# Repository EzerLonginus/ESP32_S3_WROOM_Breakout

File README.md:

# ESP32_S3_WROOM_Breakout
Breakout Board for ESP32 S3 WROOM

This board is a simple breakout for the ESP32 S3 WROOM.  The interface includes the standard reset and boot button, with a USB to UART CH340G converter, and a 3V3 regulator.  All GPIO pins are broken out to standard 2.54mm headers.  USB-C reseptacle connector is used, but at the USB 2.0 standard. 

## Purpose
This is mostly an excersize in designing an ESP32 module for inclusion in other projects.  Once this design is functional, I'll start using it as a template for more custom oriented projects involving the chip (or some variant).  I decided on the ESP S3 WROOM, because the S2 Solo seems to be slowly phasing out, and also doesn't have bluetooth functionality.  Depending on how this excersize goes, I may start designing boards with just the bare chip (no built in WiFi antenna, SPI Flash, etc).    

## Scematic

## Layout

## Current State of Affairs
### Version 1
* Populate and test board
* Upload some blink/hello world sketch
* Fix the inevitable issue that I missed during production

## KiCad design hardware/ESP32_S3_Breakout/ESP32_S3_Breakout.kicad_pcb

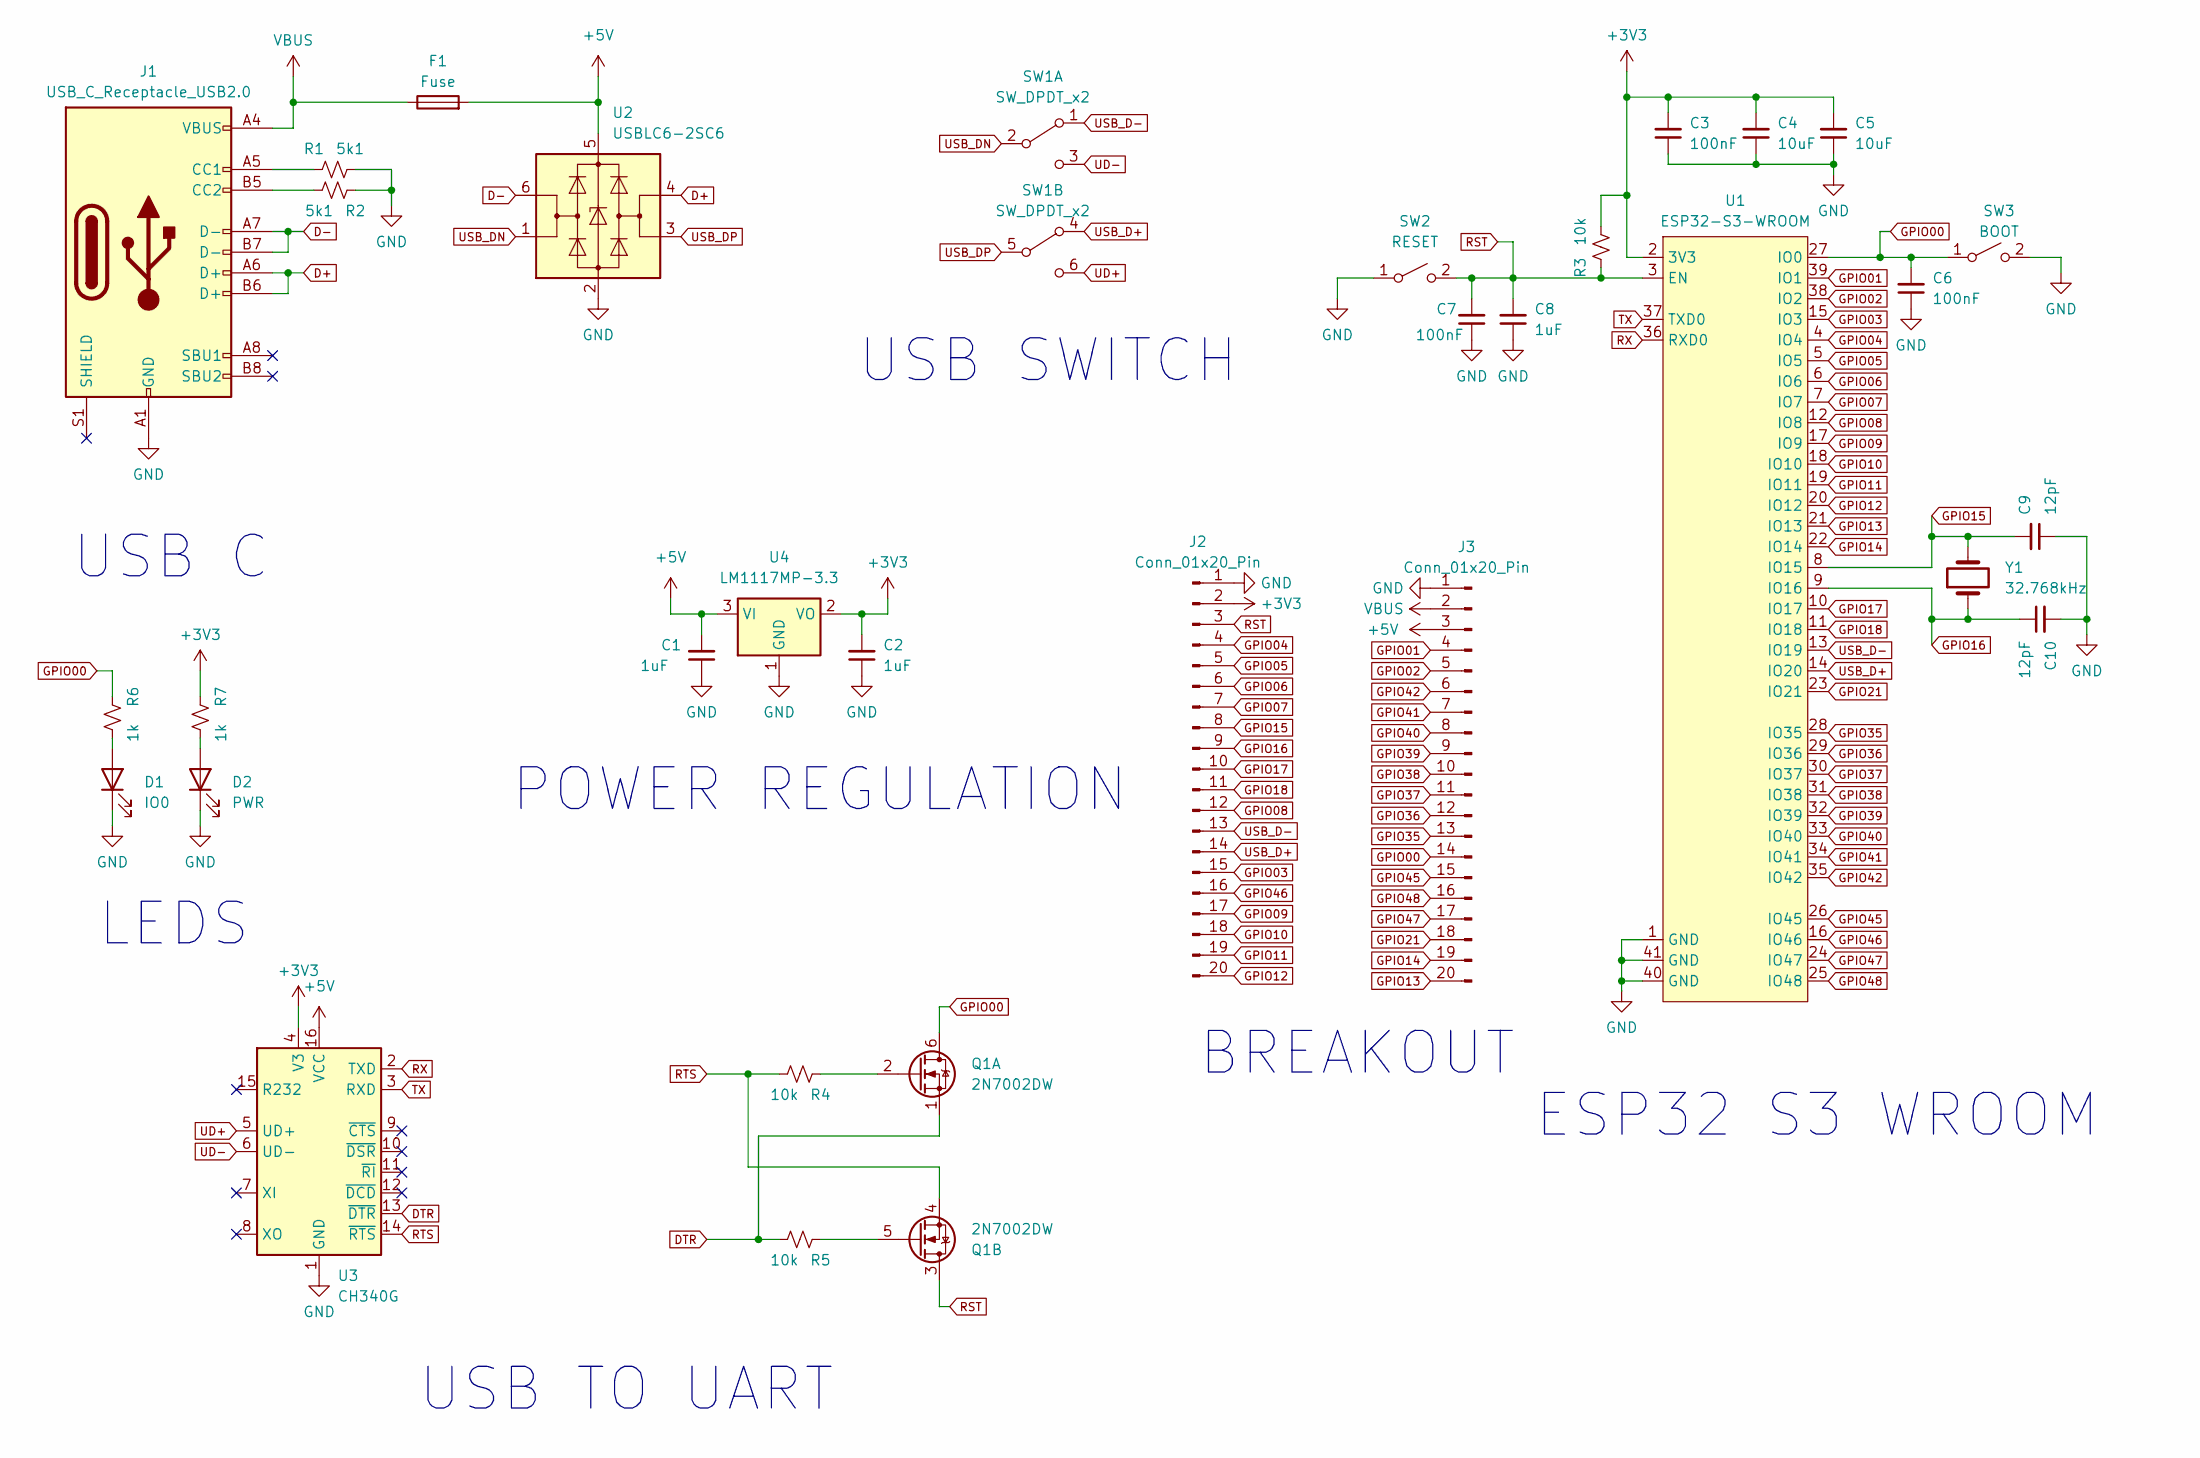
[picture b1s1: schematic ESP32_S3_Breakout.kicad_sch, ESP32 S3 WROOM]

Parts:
C1, C2, C8: 1uF; C_0603_1608Metric
C3, C6, C7: 100nF; C_0603_1608Metric
C4, C5: 10uF; C_0805_2012Metric
C9, C10: 12pF; C_0603_1608Metric
D1: IO0; LED_0603_1608Metric
D2: PWR; LED_0603_1608Metric
F1: Fuse; Fuse_0603_1608Metric
J1: USB_C_Receptacle_USB2.0; USB_C_Receptacle_G-Switch_GT-USB-7010ASV
J2, J3: Conn_01x20_Pin; PinHeader_1x20_P2.54mm_Vertical
Q1: 2N7002DW; SOT-363_SC-70-6
R1, R2: 5k1; R_0603_1608Metric
R3, R4, R5: 10k; R_0603_1608Metric
R6, R7: 1k; R_0603_1608Metric
SW1: SW_DPDT_x2; SMD DPDT Toggle SS-3235S-L1
SW2: RESET; SW_SPST_CK_RS282G05A3
SW3: BOOT; SW_SPST_CK_RS282G05A3
U1: ESP32-S3-WROOM; ESP32-S3-WROOM-1
U2: USBLC6-2SC6; SOT-23-6
U3: CH340G; SOIC-16_3.9x9.9mm_P1.27mm
U4: LM1117MP-3.3; SOT-223-3_TabPin2
Y1: 32.768kHz; Crystal_SMD_EuroQuartz_EQ161-2Pin_3.2x1.5mm_HandSoldering

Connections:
+3V3: C2.2, C3.2, C4.2, C5.2, J2.2, R3.2, R7.1, U1.2 (3V3), U3.4 (V3), U4.2 (VO)
+5V: C1.2, F1.2, J3.3, U2.5 (VBUS), U3.16 (VCC), U4.3 (VI)
D+: J1.A6 (D+), J1.B6 (D+), U2.4 (I/O2)
D-: J1.A7 (D-), J1.B7 (D-), U2.6 (I/O1)
DTR: Q1.1 (S), R5.2, U3.13 (~DTR)
GND: C1.1, C2.1, C3.1, C4.1, C5.1, C6.1, C7.1, C8.1, C9.1, C10.2, D1.1 (K), D2.1 (K), J1.A1 (GND), J1.A12 (GND), J1.B1 (GND), J1.B12 (GND), J2.1, J3.1, R1.2, R2.1, SW2.1 (A), SW3.2 (B), U1.1 (GND), U1.40 (GND), U1.41 (GND), U2.2 (GND), U3.1 (GND), U4.1 (GND)
GPIO00: C6.2, J3.14, Q1.6 (D), R6.1, SW3.1 (A), U1.27 (IO0)
GPIO01: J3.4, U1.39 (IO1)
GPIO02: J3.5, U1.38 (IO2)
GPIO03: J2.15, U1.15 (IO3)
GPIO04: J2.4, U1.4 (IO4)
GPIO05: J2.5, U1.5 (IO5)
GPIO06: J2.6, U1.6 (IO6)
GPIO07: J2.7, U1.7 (IO7)
GPIO08: J2.12, U1.12 (IO8)
GPIO09: J2.17, U1.17 (IO9)
GPIO10: J2.18, U1.18 (IO10)
GPIO11: J2.19, U1.19 (IO11)
GPIO12: J2.20, U1.20 (IO12)
GPIO13: J3.20, U1.21 (IO13)
GPIO14: J3.19, U1.22 (IO14)
GPIO15: C9.2, J2.8, U1.8 (IO15), Y1.2
GPIO16: C10.1, J2.9, U1.9 (IO16), Y1.1
GPIO17: J2.10, U1.10 (IO17)
GPIO18: J2.11, U1.11 (IO18)
GPIO21: J3.18, U1.23 (IO21)
GPIO35: J3.13, U1.28 (IO35)
GPIO36: J3.12, U1.29 (IO36)
GPIO37: J3.11, U1.30 (IO37)
GPIO38: J3.10, U1.31 (IO38)
GPIO39: J3.9, U1.32 (IO39)
GPIO40: J3.8, U1.33 (IO40)
GPIO41: J3.7, U1.34 (IO41)
GPIO42: J3.6, U1.35 (IO42)
GPIO45: J3.15, U1.26 (IO45)
GPIO46: J2.16, U1.16 (IO46)
GPIO47: J3.17, U1.24 (IO47)
GPIO48: J3.16, U1.25 (IO48)
unnamed: D1.2 (A), R6.2
unnamed: D2.2 (A), R7.2
unnamed: J1.A5 (CC1), R1.1
unnamed: J1.B5 (CC2), R2.2
unnamed: Q1.2 (G), R4.1
unnamed: Q1.5 (G), R5.1
RST: C7.2, C8.2, J2.3, Q1.3 (D), R3.1, SW2.2 (B), U1.3 (EN)
RTS: Q1.4 (S), R4.2, U3.14 (~RTS)
RX: U1.36 (RXD0), U3.2 (TXD)
TX: U1.37 (TXD0), U3.3 (RXD)
UD+: SW1.6 (C), U3.5 (UD+)
UD-: SW1.3 (C), U3.6 (UD-)
USB_D+: J2.14, SW1.4 (A), U1.14 (IO20)
USB_D-: J2.13, SW1.1 (A), U1.13 (IO19)
USB_DN: SW1.2 (B), U2.1 (I/O1)
USB_DP: SW1.5 (B), U2.3 (I/O2)
VBUS: F1.1, J1.A4 (VBUS), J1.A9 (VBUS), J1.B4 (VBUS), J1.B9 (VBUS), J3.2

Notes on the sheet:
USB C
BREAKOUT
LEDS
ESP32 S3 WROOM
USB TO UART
USB SWITCH
POWER REGULATION

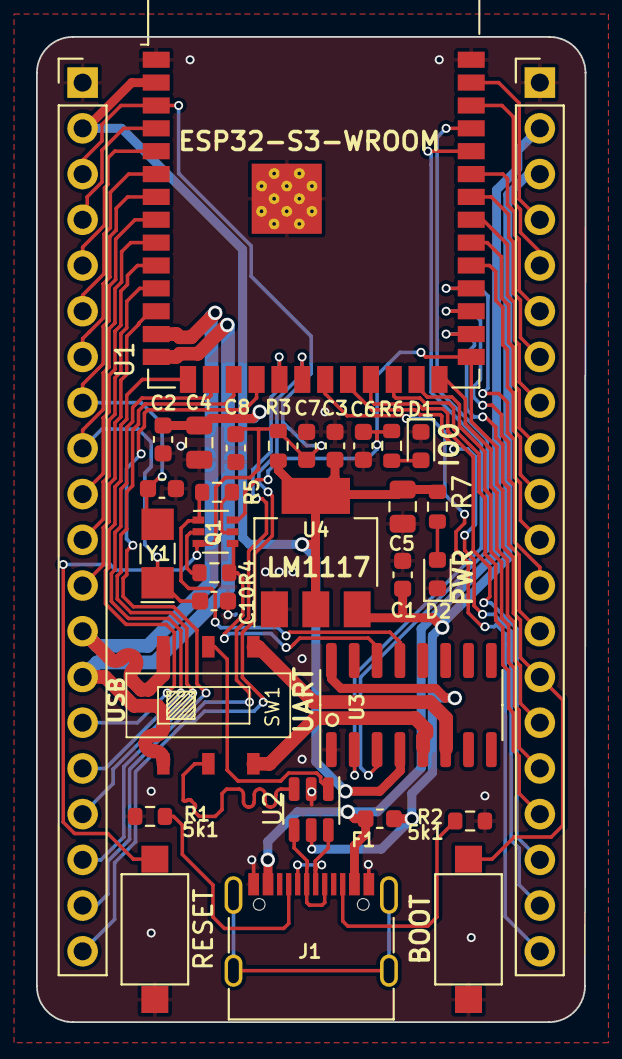
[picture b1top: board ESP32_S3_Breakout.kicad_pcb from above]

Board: 2 copper layers, 30.5 x 54.7 mm, 32 parts (0 on the bottom side), 55 nets.

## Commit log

2024-05-27 Initial Commit for ESP32 S3 design
2024-06-24 Version 02 - Added LEDs
